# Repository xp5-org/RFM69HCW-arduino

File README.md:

the RFM69HCW can be tested with the arduino, ive wired it up in this way following a breakout board from sparkfun https://github.com/sparkfun/RFM69HCW_Breakout

for testing, i used low power labs gateway.ino from their library

included in this repro is the eagle files for my test circuit 

no guarantees its correct use the schematic at your own risk

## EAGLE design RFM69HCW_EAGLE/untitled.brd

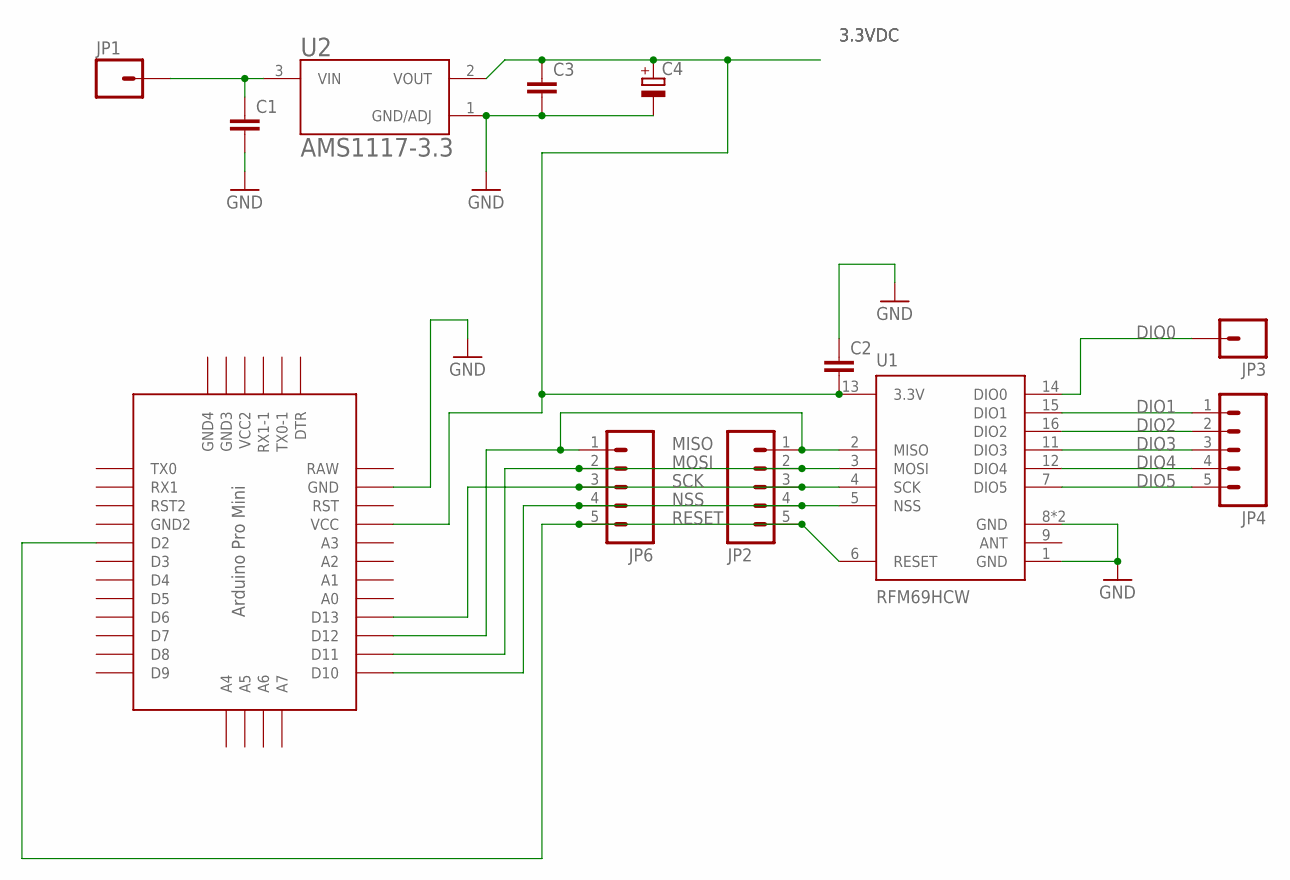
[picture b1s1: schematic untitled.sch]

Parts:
C1, C2, C3: C-EU025-030X050; C025-030X050
C4: CPOL-EUE5-8.5; E5-8,5
JP1, JP3: M01SMDNS; 1X01NS
JP2, JP4, JP6: M05_ROUNDONLY_NOSILK; 1X05_ROUNDONLY_NOSILK
U1: RFM69HCW; RFM69HCW-XXXS2
U2: AMS1117-3.3; SOT229P700X180-4N
U$1: PRO-MINI

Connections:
3.3VDC: C2.2, C3.1, C4.+, U1.13 (3.3V), U2.2 (VOUT), U$1.VCC
DIO0: JP3.1, U1.14 (DIO0)
DIO1: JP4.1, U1.15 (DIO1)
DIO2: JP4.2, U1.16 (DIO2)
DIO3: JP4.3, U1.11 (DIO3)
DIO4: JP4.4, U1.12 (DIO4)
DIO5: JP4.5, U1.7 (DIO5)
GND: C1.2, C2.1, C3.2, C4.-, U1.1 (GND), U1.8 (GND), U1.10 (GND), U2.1 (GND/ADJ), U$1.GND
MISO: JP2.1, JP6.1, U1.2 (MISO), U$1.D12
MOSI: JP2.2, JP6.2, U1.3 (MOSI), U$1.D11
unnamed: C1.1, JP1.1, U2.3 (VIN)
NSS: JP2.4, JP6.4, U1.5 (NSS), U$1.D10
RAW: U$1.RAW
RESET: JP2.5, JP6.5, U1.6 (RESET), U$1.D2
SCK: JP2.3, JP6.3, U1.4 (SCK), U$1.D13

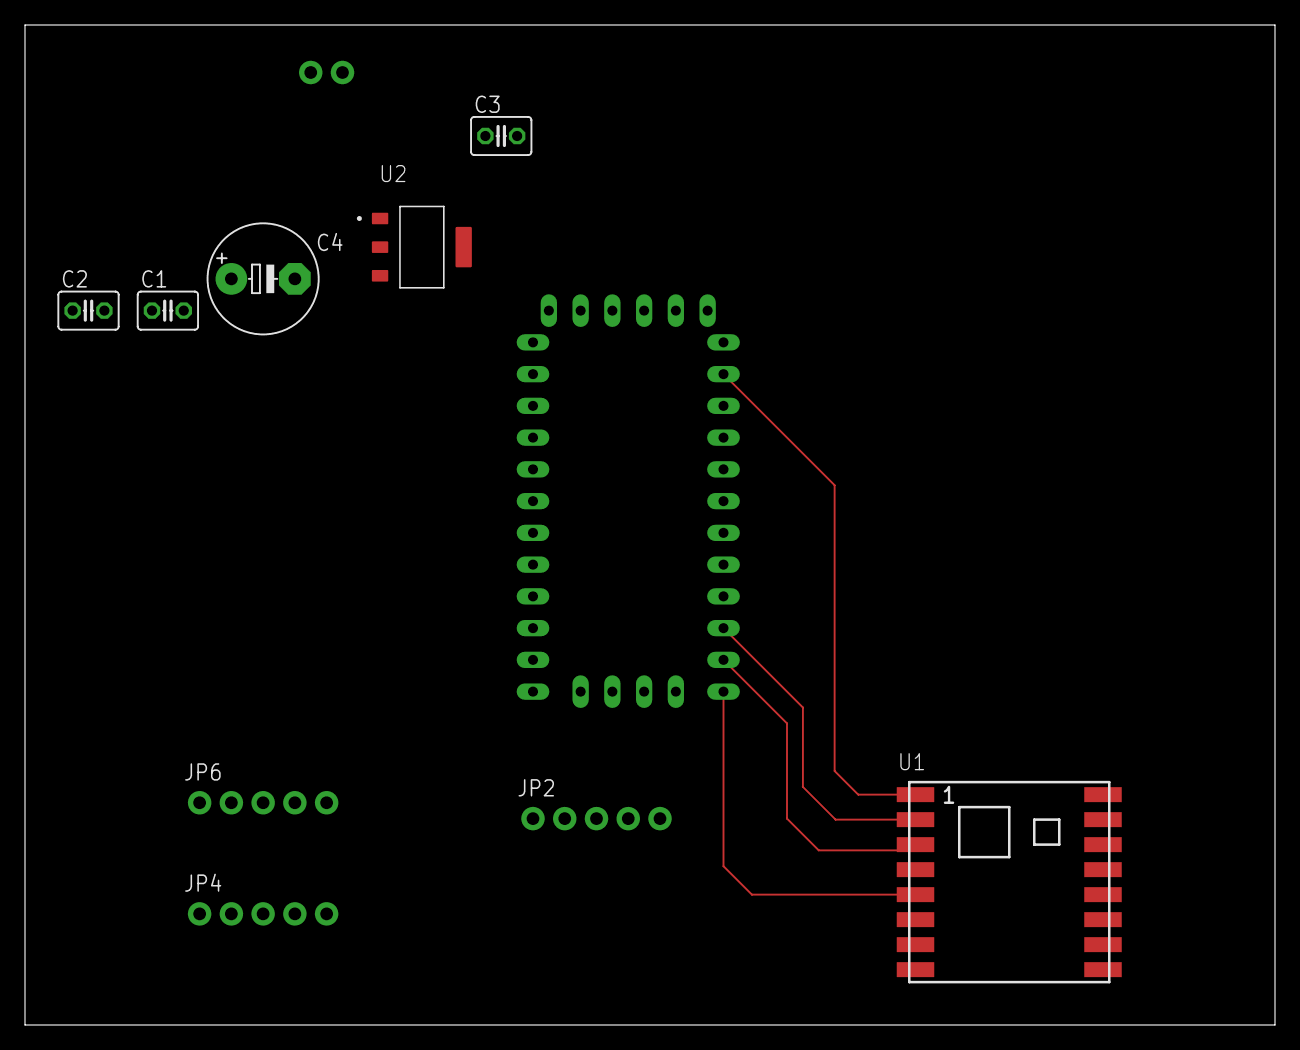
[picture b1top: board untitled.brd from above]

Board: 2 copper layers, 100.0 x 80.0 mm, 12 parts (0 on the bottom side), 14 nets.

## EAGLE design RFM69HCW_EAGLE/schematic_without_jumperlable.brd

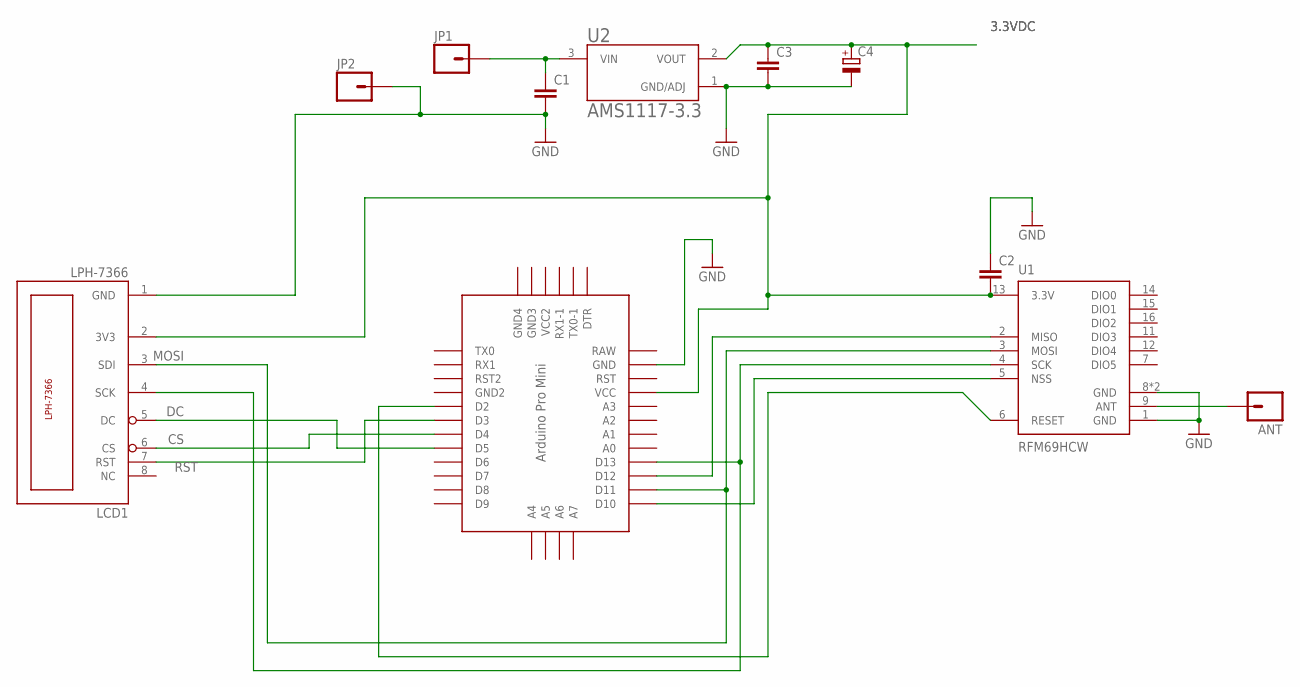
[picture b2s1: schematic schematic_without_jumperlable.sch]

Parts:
ANT: M01SMDNS; 1X01NS
C1, C2, C3: C-EU025-030X050; C025-030X050
C4: CPOL-EUE5-8.5; E5-8,5
JP1, JP2: M01SMDNS; 1X01NS
LCD1: LPH-7366
U1: RFM69HCW; RFM69HCW-XXXS2
U2: AMS1117-3.3; SOT229P700X180-4N
U$1: PRO-MINI

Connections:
3.3VDC: C2.2, C3.1, C4.+, LCD1.2 (3V3), U1.13 (3.3V), U2.2 (VOUT), U$1.VCC
ANT: ANT.1, U1.9 (ANT)
CS: LCD1.6 (CS), U$1.D4
DC: LCD1.5 (DC), U$1.D5
GND: C1.2, C2.1, C3.2, C4.-, JP2.1, LCD1.1 (GND), U1.1 (GND), U1.8 (GND), U1.10 (GND), U2.1 (GND/ADJ), U$1.GND
MISO: U1.2 (MISO), U$1.D12
MOSI: LCD1.3 (SDI), U1.3 (MOSI), U$1.D11
NSS: U1.5 (NSS), U$1.D10
RAW: U$1.RAW
RESET: U1.6 (RESET), U$1.D2
RST: LCD1.7 (RST), U$1.D3
SCK: LCD1.4 (SCK), U1.4 (SCK), U$1.D13
VIN: C1.1, JP1.1, U2.3 (VIN)

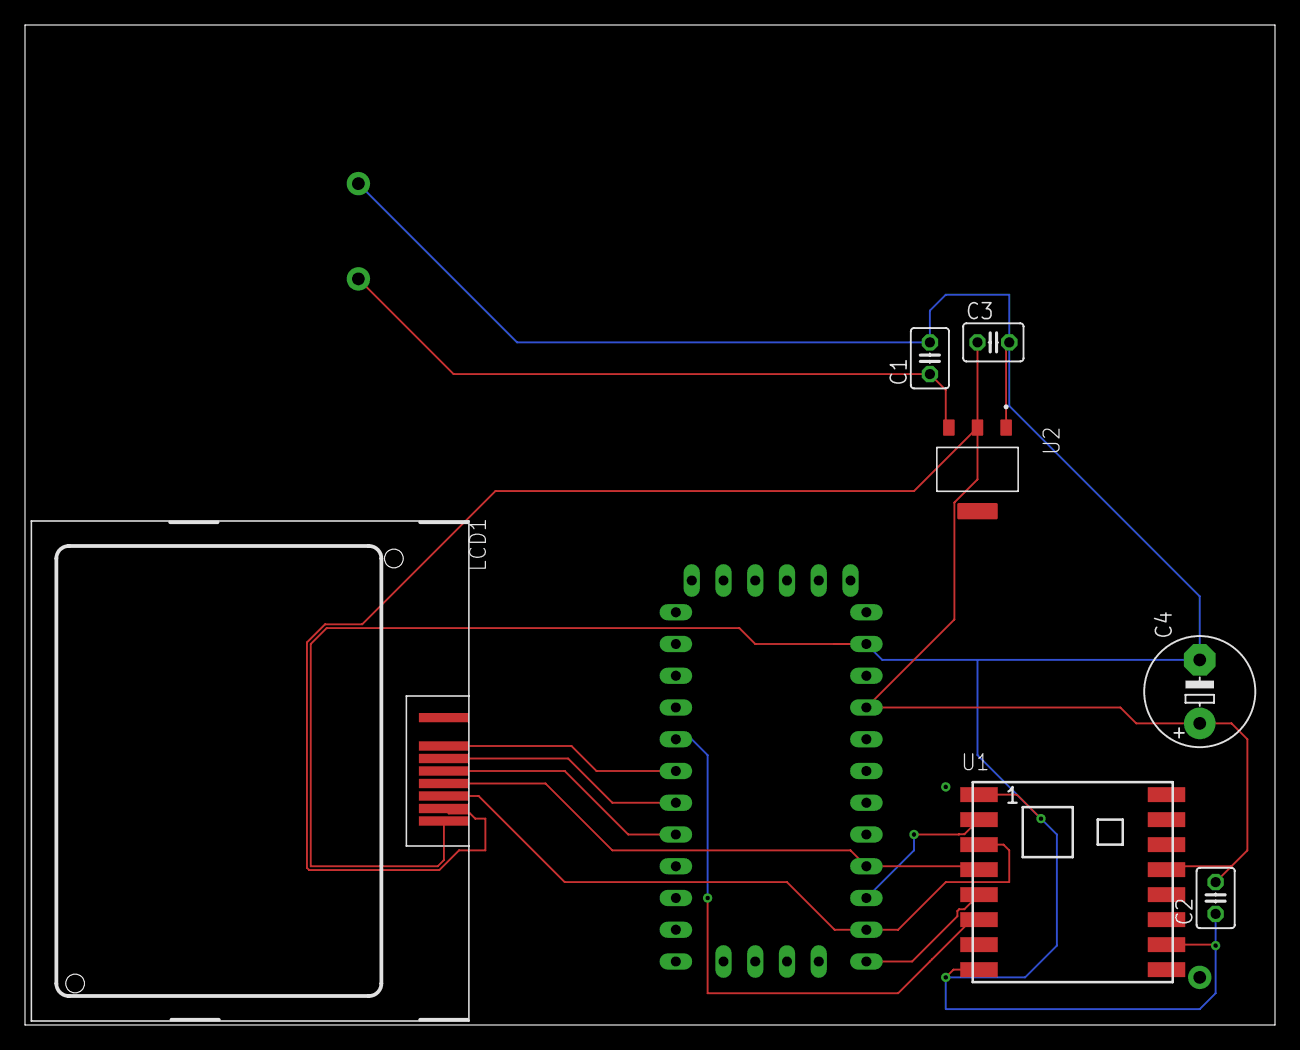
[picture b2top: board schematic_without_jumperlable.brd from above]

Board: 2 copper layers, 100.0 x 80.0 mm, 11 parts (0 on the bottom side), 12 nets.

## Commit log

2024-01-12 added eagle files
    RFM69HCW eagle files for arduino test , using this as a reference https://github.com/sparkfun/RFM69HCW_Breakout

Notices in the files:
parts and their libraries:
SparkFun-Aesthetics: Licensing: CC v3.0 Share-Alike You are welcome to use this library for commercial purposes.
